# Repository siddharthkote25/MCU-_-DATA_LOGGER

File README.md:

# Mcu Data Logger

A compact, battery-backed data logger board built around the ATmega328P-AU. It has a real-time clock for timestamping and 2 Mbit of external I²C EEPROM for storage, and it breaks out I²C, UART, GPIO and ICSP headers for sensors and programming. Designed end-to-end in **KiCad 10**.

## Features

- **MCU:** ATmega328P-AU (TQFP-32) with a 16 MHz crystal and 22 pF load capacitors
- **Real-time clock:** DS1337 with a 32.768 kHz crystal, battery backup, and pull-ups on its SQW/INTA outputs
- **Storage:** 2 × 24LC1025 (1 Mbit each, 2 Mbit / 256 KB total) I²C EEPROMs, write-protect tied to GND
- **I²C bus:** 4.7 kΩ pull-ups on SDA/SCK, shared by the RTC and both EEPROMs
- **Indicators:** power LED and a status LED on SCK (D13)
- **Programming:** standard 2×3 ICSP header, with a 10 kΩ pull-up on RESET
- **Power:** battery input with decoupling on every IC, plus AREF filter capacitor
- **Mechanical:** four mounting holes, one in each corner

## Connectors

| Ref | Interface | Pins |
|-----|-----------|------|
| J1 | I²C | GND, VCC, SDA, SCK |
| J2 | GPIO | D2–D8, GND, VCC |
| J3 | Serial / UART | GND, VCC, RX, TX |
| J4 | ICSP | MISO, VCC, SCK, MOSI, RESET, GND |
| Battery | Power input | VCC, GND |

## Schematic

Hierarchical design, split into functional blocks:

- **MCU:** ATmega328P, crystal, reset circuit, LEDs, AREF filter
- **Real time clock:** DS1337, 32.768 kHz crystal, pull-ups, decoupling
- **EEPROM:** two 24LC1025 with address pins, write-protect and I²C pull-ups
- **Connectors:** I²C, UART, GPIO and ICSP (separate sub-sheet)
- **Mounting:** four mounting holes

**Sheet 1: MCU, RTC, EEPROM**

**Sheet 2: Connectors**

## PCB

- Layers: 2-layer
- Board size: [XX mm × XX mm]
- Components: mostly SMD (0603/0805 passives, TQFP-32, SOIC-8), through-hole headers
- Copper fills, silkscreen labelling for all connectors, DRC clean

## Repository Structure

```
.
├── ATMEGA328P-AU/               # MCU symbol / footprint / 3D model files
├── Footprints/                  # Custom footprint library
├── Gerbers/                     # Manufacturing outputs (Gerber + drill files)
├── symbols-downloaded/          # Downloaded symbol libraries
├── Mcu - data logger.kicad_pro  # KiCad project file
├── Mcu - data logger.kicad_sch  # Top-level schematic
├── Connectors.kicad_sch         # Connectors sub-sheet
├── Mcu - data logger.kicad_pcb  # PCB layout
├── sym-lib-table                # Project symbol library table
├── report.txt                   # Gerber/drill generation report
├── 3D view.png
├── Layout Design.png
├── Mcu sheet 1.png
├── Mcu sheet 2 .png
└── README.md
```

## Tools

- KiCad 10.0.6
- Git / GitHub for version control

## My details

**Siddharth Kote**
siddharthkote129@gmail.com

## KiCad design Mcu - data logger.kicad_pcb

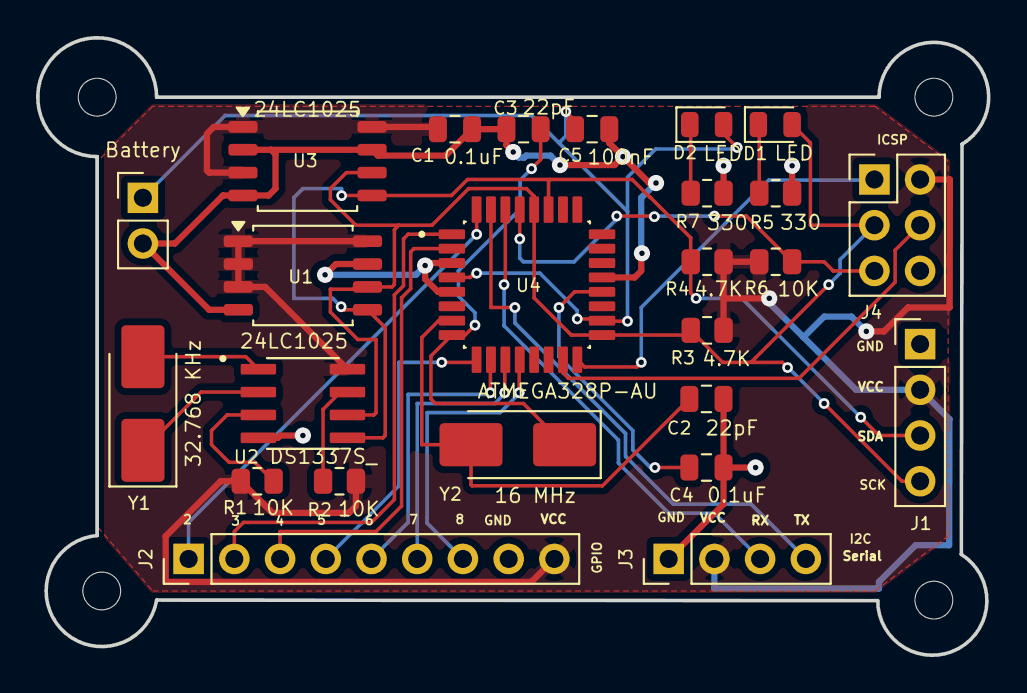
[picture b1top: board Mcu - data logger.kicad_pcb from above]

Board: 2 copper layers, 52.8 x 34.3 mm, 29 parts (0 on the bottom side), 26 nets.

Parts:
BT1: Battery; PinHeader_1x02_P2.54mm_Vertical
C1, C4: 0.1uF; C_0805_2012Metric
C2, C3: 22pF; C_0805_2012Metric
C5: 100nF; C_0805_2012Metric
D1, D2: LED; LED_0805_2012Metric
H1, H2, H3, H4: MountingHole; MountingHole_2.1mm
J1, J3: Conn_01x04_Pin; PinHeader_1x04_P2.54mm_Vertical
J2: Conn_01x09_Pin; PinHeader_1x09_P2.54mm_Vertical
J4: Conn_02x03_Odd_Even; PinHeader_2x03_P2.54mm_Vertical
R1, R2, R6: 10K; R_0805_2012Metric
R3, R4: 4.7K; R_0805_2012Metric
R5, R7: 330; R_0805_2012Metric
U1, U3: 24LC1025; SOIC-8_5.3x5.3mm_P1.27mm
U2: DS1337S_; SOIC127P600X175-8N
U4: ATMEGA328P-AU; QFP80P900X900X120-32N
Y1: 32.768 KHz; Crystal_SMD_5032-2Pin_5.0x3.2mm_HandSoldering
Y2: 16 MHz; Crystal_SMD_5032-2Pin_5.0x3.2mm_HandSoldering

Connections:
/D2: J2.1, U4.32 (PD2)
/D3: J2.2, U4.1 (PD3)
/D4: J2.3, U4.2 (PD4)
/D5: J2.4, U4.9 (PD5)
/D6: J2.5, U4.10 (PD6)
/D7: J2.6, U4.11 (PD7)
/D8: J2.7, U4.12 (PB0)
/MISO: J4.1, U4.16 (PB4)
/MOSI: J4.4, U4.15 (PB3)
/RESET: J4.5, R6.2, U4.29 (PC6/~RESET)
/RX: J3.3, U4.30 (PD0)
/SCK: D1.2 (A), J1.4, J4.3, R3.2, U1.6 (SCL), U2.6 (SCL), U3.6 (SCL), U4.17 (PB5), U4.28 (PC5)
/SDA: J1.3, R4.1, U1.5 (SDA), U2.5 (SDA), U3.5 (SDA), U4.27 (PC4)
/TX: J3.4, U4.31 (PD1)
/VCC: C1.2, J1.2, J2.9, J3.2, J4.2, R1.1, R2.1, R3.1, R4.2, R6.1, U1.1 (A0), U1.2 (A1), U1.3 (A2), U1.8 (VCC), U2.8 (VCC), U3.1 (A0), U3.3 (A2), U3.8 (VCC)
GND: BT1.2 (-), C1.1, C2.2, C3.1, C4.1, C5.2, J1.1, J2.8, J3.1, J4.6, R5.1, R7.2, U1.4 (GND), U1.7 (WP), U2.4 (GND), U3.2 (A1), U3.4 (GND), U3.7 (WP), U4.3 (GND), U4.5 (GND), U4.21 (GND)
unnamed: BT1.1 (+), C5.1, D2.2 (A), U4.4 (VCC), U4.18 (AVCC)
unnamed: D1.1 (K), R5.2
unnamed: D2.1 (K), R7.1
unnamed: R2.2, U2.7 (SQW/~INT)
unnamed: U2.1 (X1), Y1.2
unnamed: U2.2 (X2), Y1.1
unnamed: R1.2, U2.3 (~INTA)
unnamed: C4.2, U4.20 (AREF)
unnamed: C2.1, U4.7 (PB6), Y2.2
unnamed: C3.2, U4.8 (PB7), Y2.1
